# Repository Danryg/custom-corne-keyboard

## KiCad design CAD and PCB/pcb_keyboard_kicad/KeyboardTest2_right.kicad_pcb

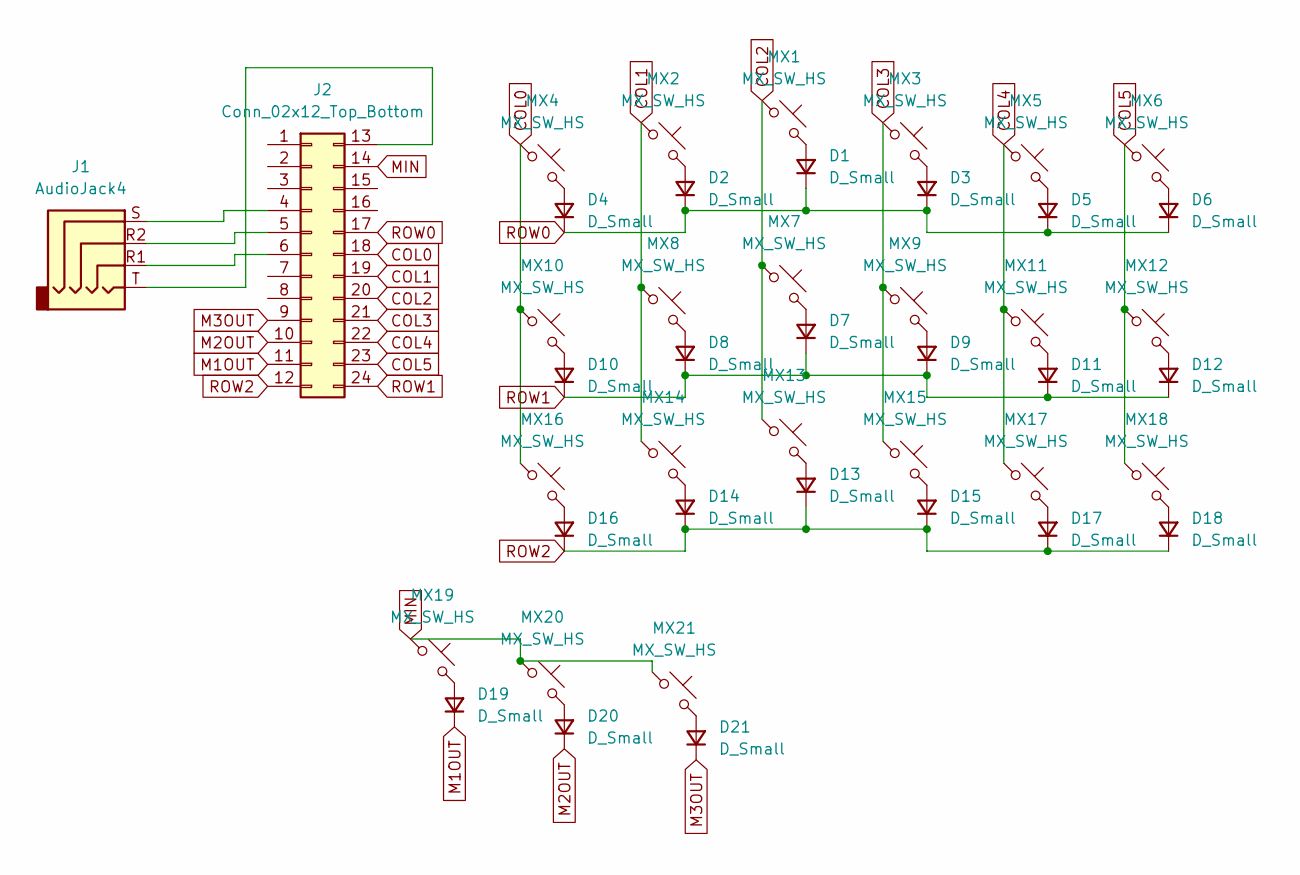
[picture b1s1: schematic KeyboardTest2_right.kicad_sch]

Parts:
D1, D2, D3, D4, D5, D6, D7, D8, D9, D10, D11, D12, D13, D14, D15, D16, D17, D18, D19, D20, D21: D_Small; D_SOD-123
J1: AudioJack4; Jack_3.5mm_KoreanHropartsElec_PJ-320D-4A_Horizontal
J2: Conn_02x12_Top_Bottom; ProMicro_USBup
MX1, MX2, MX3, MX4, MX5, MX6, MX7, MX8, MX9, MX10, MX11, MX12, MX13, MX14, MX15, MX16, MX17, MX18, MX19, MX20, MX21: MX_SW_HS; SW_MX_HS_CPG151101S11_1u

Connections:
COL0: J2.18, MX4.1, MX10.1, MX16.1
COL1: J2.19, MX2.1, MX8.1, MX14.1
COL2: J2.20, MX1.1, MX7.1, MX13.1
COL3: J2.21, MX3.1, MX9.1, MX15.1
COL4: J2.22, MX5.1, MX11.1, MX17.1
COL5: J2.23, MX6.1, MX12.1, MX18.1
M1OUT: D19.1 (K), J2.11
M2OUT: D20.1 (K), J2.10
M3OUT: D21.1 (K), J2.9
MIN: J2.14, MX19.1, MX20.1, MX21.1
unnamed: D1.2 (A), MX1.2
unnamed: D2.2 (A), MX2.2
unnamed: D3.2 (A), MX3.2
unnamed: D4.2 (A), MX4.2
unnamed: D5.2 (A), MX5.2
unnamed: D6.2 (A), MX6.2
unnamed: D7.2 (A), MX7.2
unnamed: D8.2 (A), MX8.2
unnamed: D9.2 (A), MX9.2
unnamed: D10.2 (A), MX10.2
unnamed: D11.2 (A), MX11.2
unnamed: D12.2 (A), MX12.2
unnamed: D13.2 (A), MX13.2
unnamed: D14.2 (A), MX14.2
unnamed: D15.2 (A), MX15.2
unnamed: D16.2 (A), MX16.2
unnamed: D17.2 (A), MX17.2
unnamed: D18.2 (A), MX18.2
unnamed: D19.2 (A), MX19.2
unnamed: D20.2 (A), MX20.2
unnamed: D21.2 (A), MX21.2
unnamed: J1.S, J2.4
unnamed: J1.R2, J2.5
unnamed: J1.R1, J2.6
unnamed: J1.T, J2.13
ROW0: D1.1 (K), D2.1 (K), D3.1 (K), D4.1 (K), D5.1 (K), D6.1 (K), J2.17
ROW1: D7.1 (K), D8.1 (K), D9.1 (K), D10.1 (K), D11.1 (K), D12.1 (K), J2.24
ROW2: D13.1 (K), D14.1 (K), D15.1 (K), D16.1 (K), D17.1 (K), D18.1 (K), J2.12

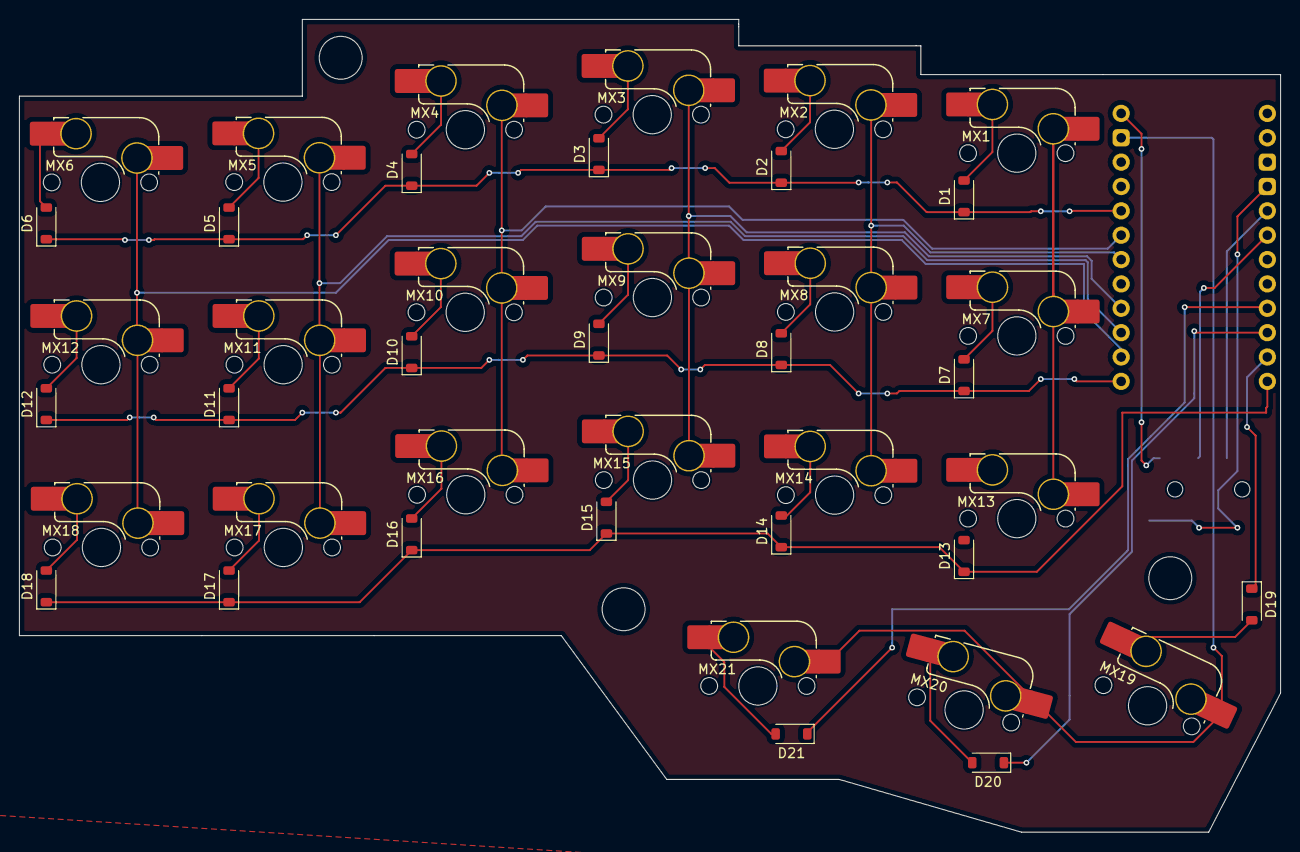
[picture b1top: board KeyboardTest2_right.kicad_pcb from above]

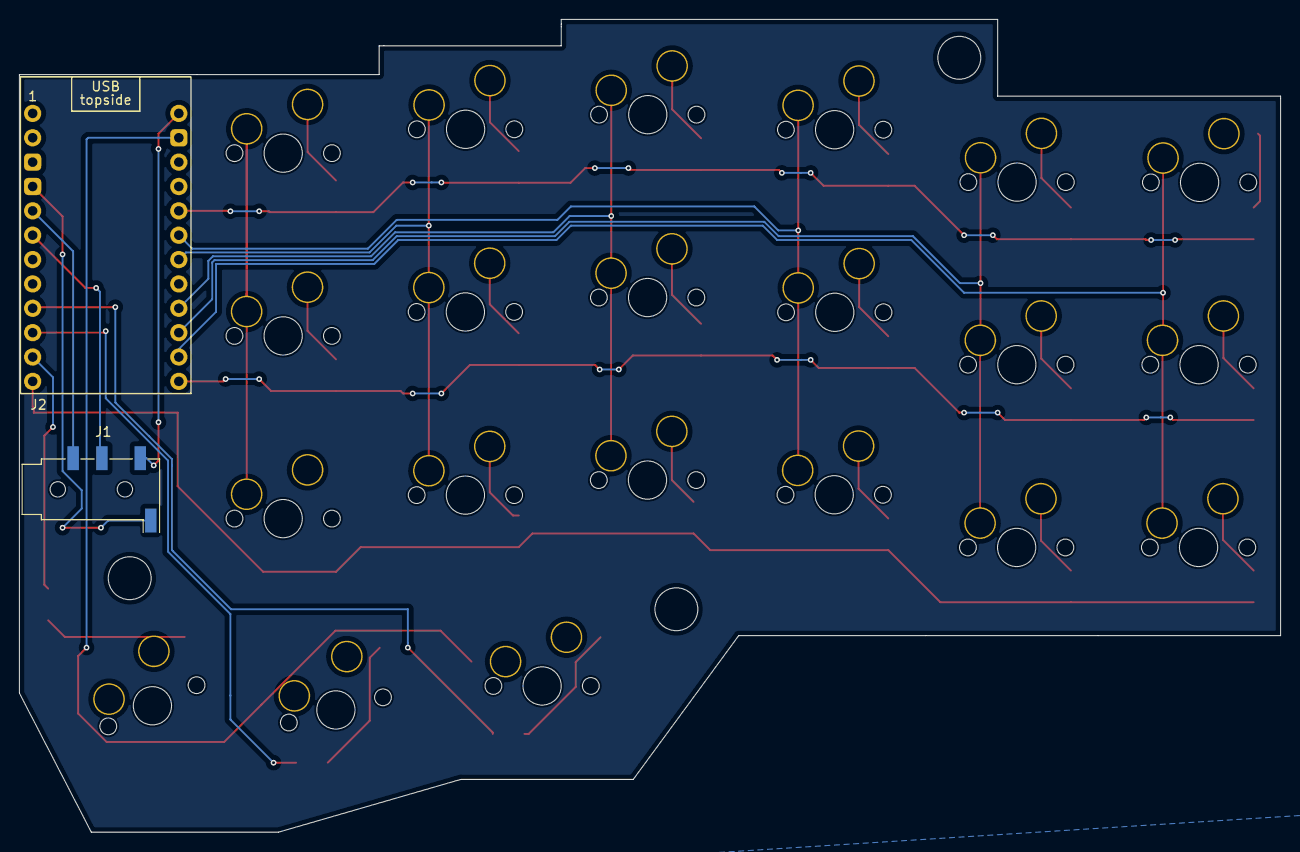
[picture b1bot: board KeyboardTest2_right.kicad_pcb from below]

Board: 2 copper layers, 131.5 x 84.8 mm, 44 parts (2 on the bottom side), 38 nets.

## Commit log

2024-05-21 Everything
2024-05-22 3D cad and pcb layout
2024-09-02 Updated cad models
2024-09-02 Add: Left case stld files
2024-09-02 Removed redundant files
2024-09-04 Stuff
2024-09-05 New key mappings
2024-09-18 new strucuture and cad fiels for right case
